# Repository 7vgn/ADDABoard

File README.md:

# AD/DA Board evolved
## An Add-On for the ATmega644(A) Evaluation Board

This is an add-on for the [EvaBoard evolved](https://github.com/7vgn/EvaBoard/) ATmega644(A) evaluation board. It is inspired by (and compatible with) the add-on board used in the lab course "Praktikum Systemprogrammierung" in the computer science curriculum at RWTH Aachen. It can be used both with the original [evaluation board](https://www.embedded.rwth-aachen.de/doku.php?id=lehre:atmegaevaboard) and its remake. 

This repository contains:

- A richly illustrated [Guide Book](Guide/ADDABoardGuide.pdf) with everything you need to know to build and use the board
- A [KiCAD project](KiCAD/) with the [Schematic](KiCAD/Schematic.pdf) and a PCB layout, ready to be manufactured
- The [bill of materials](BOM/BOM.pdf)
- [Test code](Tests/) for testing and debugging the board

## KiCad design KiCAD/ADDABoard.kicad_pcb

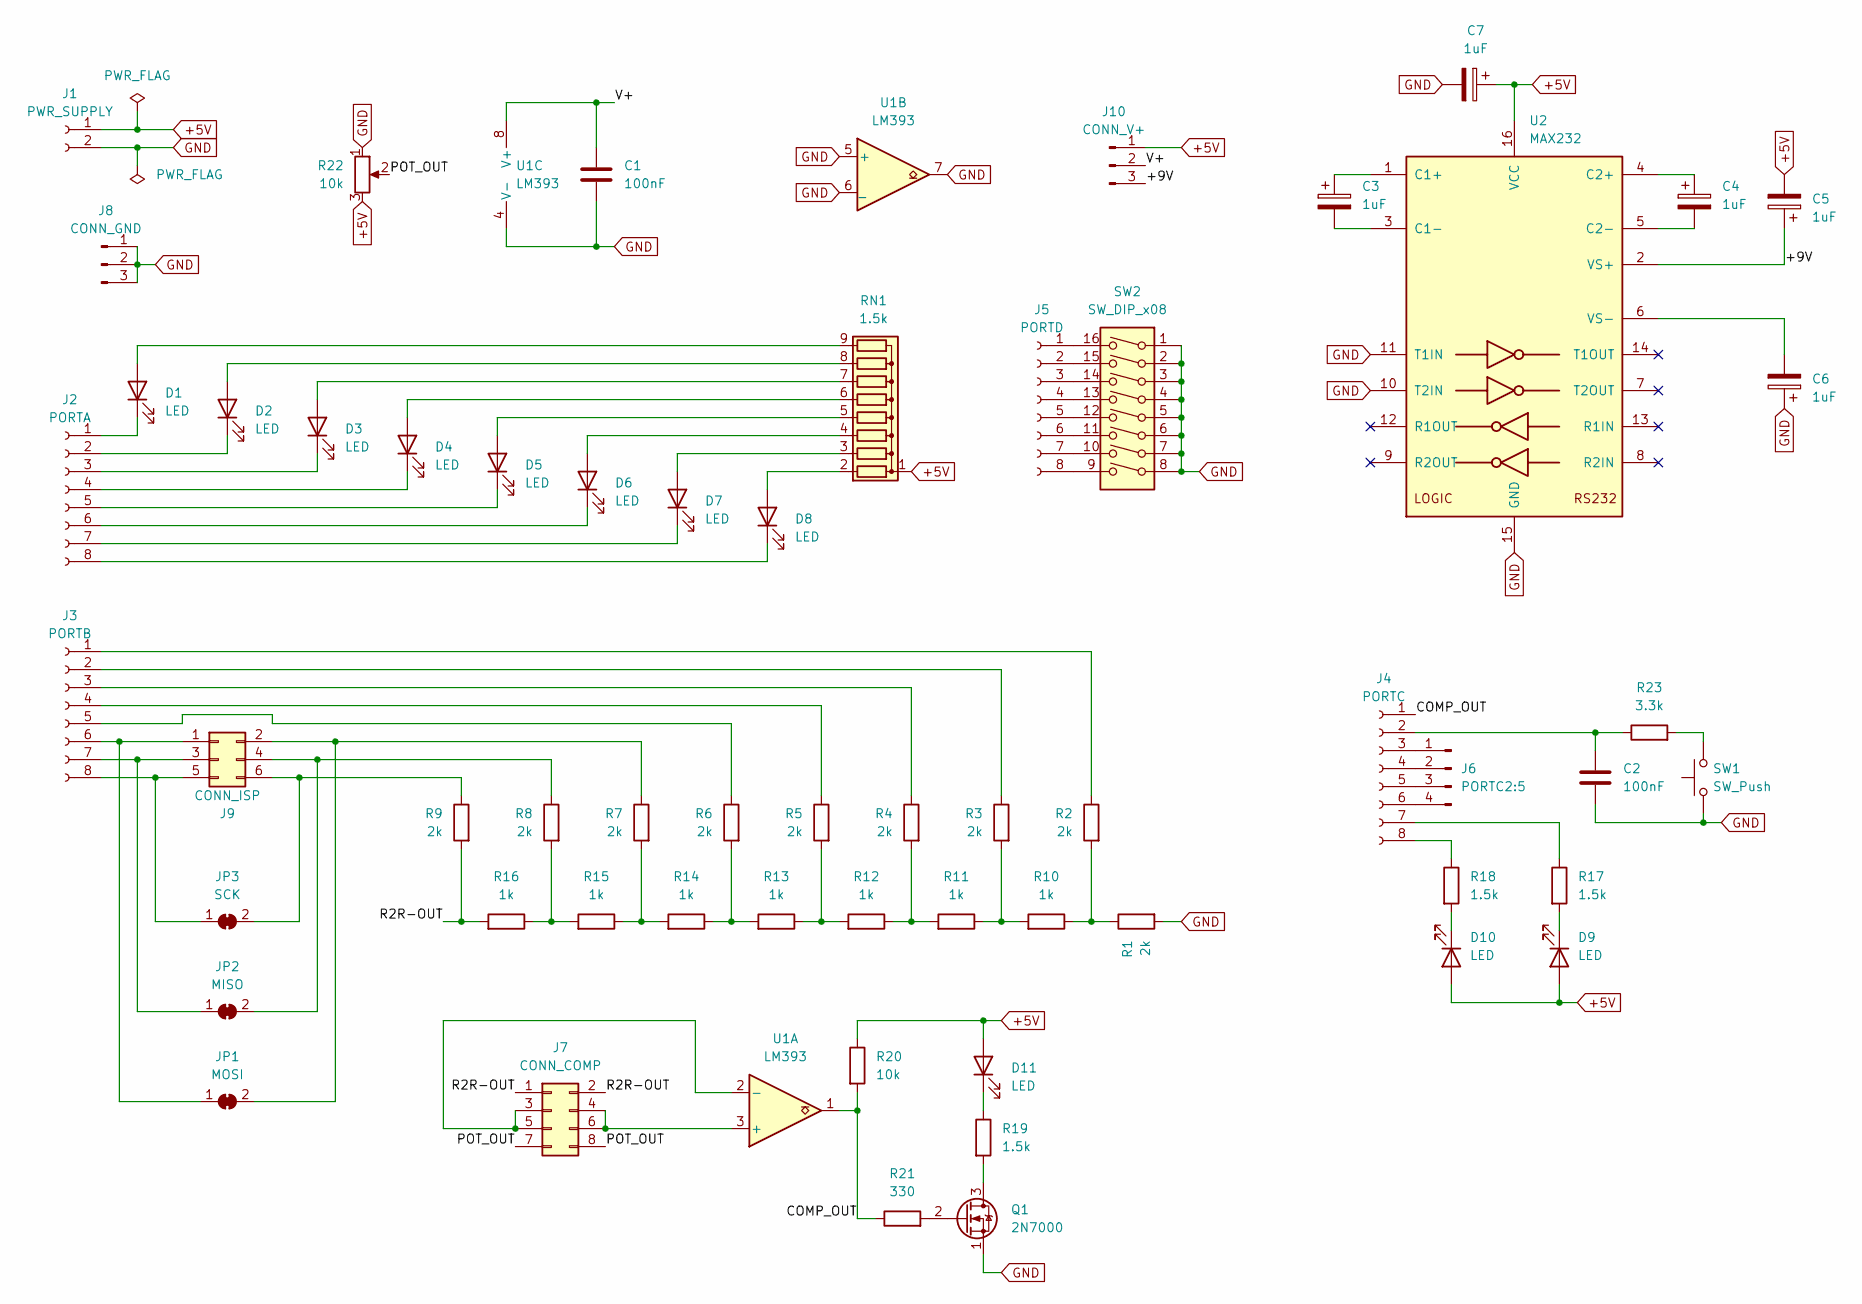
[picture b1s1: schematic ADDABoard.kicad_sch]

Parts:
C1, C2: 100nF; C_Disc_D5.0mm_W2.5mm_P5.00mm
C3, C4, C5, C6, C7: 1uF; CP_Radial_D5.0mm_P2.00mm
D1, D2, D3, D4, D5, D6, D7, D8, D9, D10, D11: LED; LED_D3.0mm
J1: PWR_SUPPLY; PinSocket_1x02_P2.54mm_Vertical
J2: PORTA; PinSocket_1x08_P2.54mm_Vertical
J3: PORTB; PinSocket_1x08_P2.54mm_Vertical
J4: PORTC; PinSocket_1x08_P2.54mm_Vertical
J5: PORTD; PinSocket_1x08_P2.54mm_Vertical
J6: PORTC2:5; PinHeader_1x04_P2.54mm_Vertical
J7: CONN_COMP; PinHeader_2x04_P2.54mm_Vertical
J8: CONN_GND; PinHeader_1x03_P2.54mm_Vertical
J9: CONN_ISP; PinHeader_2x03_P2.54mm_Vertical
J10: CONN_V+; PinHeader_1x03_P2.54mm_Vertical
JP1: MOSI; SolderJumper-2_P1.3mm_Bridged_RoundedPad1.0x1.5mm
JP2: MISO; SolderJumper-2_P1.3mm_Bridged_RoundedPad1.0x1.5mm
JP3: SCK; SolderJumper-2_P1.3mm_Bridged_RoundedPad1.0x1.5mm
Q1: 2N7000; TO-92_Inline
R1, R2, R3, R4, R5, R6, R7, R8, R9: 2k; R_Axial_DIN0207_L6.3mm_D2.5mm_P10.16mm_Horizontal
R10, R11, R12, R13, R14, R15, R16: 1k; R_Axial_DIN0207_L6.3mm_D2.5mm_P10.16mm_Horizontal
R17, R18, R19: 1.5k; R_Axial_DIN0207_L6.3mm_D2.5mm_P10.16mm_Horizontal
R20: 10k; R_Axial_DIN0207_L6.3mm_D2.5mm_P10.16mm_Horizontal
R21: 330; R_Axial_DIN0207_L6.3mm_D2.5mm_P10.16mm_Horizontal
R22: 10k; Potentiometer_Alps_RK09K_Single_Horizontal
R23: 3.3k; R_Axial_DIN0207_L6.3mm_D2.5mm_P10.16mm_Horizontal
RN1: 1.5k; R_Array_SIP9
SW1: SW_Push; SW_PUSH_6mm
SW2: SW_DIP_x08; SW_DIP_SPSTx08_Slide_9.78x22.5mm_W7.62mm_P2.54mm
U1: LM393; DIP-8_W7.62mm
U2: MAX232; DIP-16_W7.62mm

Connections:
+5V: C5.2, C7.1, D9.2 (A), D10.2 (A), D11.2 (A), J1.1, J10.1, R20.1, R22.3, RN1.1 (common), U2.16 (VCC)
/+9V: C5.1, J10.3, U2.2 (VS+)
/COMP_OUT: J4.1, R20.2, R21.1, U1.1
/POT_OUT: J7.7, J7.8, R22.2
/R2R-OUT: J7.1, J7.2, R9.2, R16.2
/V+: C1.1, J10.2, U1.8 (V+)
GND: C1.2, C2.2, C6.1, C7.2, J1.2, J8.1, J8.2, J8.3, Q1.1 (S), R1.2, R22.1, SW1.1, SW2.1, SW2.2, SW2.3, SW2.4, SW2.5, SW2.6, SW2.7, SW2.8, U1.4 (V-), U1.5 (+), U1.6 (_), U1.7, U2.10 (T2IN), U2.11 (T1IN), U2.15 (GND)
unnamed: C2.1, J4.2, R23.1
unnamed: C3.1, U2.1 (C1+)
unnamed: C3.2, U2.3 (C1-)
unnamed: C4.1, U2.4 (C2+)
unnamed: C4.2, U2.5 (C2-)
unnamed: C6.2, U2.6 (VS-)
unnamed: D1.1 (K), J2.1
unnamed: D1.2 (A), RN1.9 (R8)
unnamed: D2.1 (K), J2.2
unnamed: D2.2 (A), RN1.8 (R7)
unnamed: D3.1 (K), J2.3
unnamed: D3.2 (A), RN1.7 (R6)
unnamed: D4.1 (K), J2.4
unnamed: D4.2 (A), RN1.6 (R5)
unnamed: D5.1 (K), J2.5
unnamed: D5.2 (A), RN1.5 (R4)
unnamed: D6.1 (K), J2.6
unnamed: D6.2 (A), RN1.4 (R3)
unnamed: D7.1 (K), J2.7
unnamed: D7.2 (A), RN1.3 (R2)
unnamed: D8.1 (K), J2.8
unnamed: D8.2 (A), RN1.2 (R1)
unnamed: D9.1 (K), R17.2
unnamed: D10.1 (K), R18.2
unnamed: D11.1 (K), R19.1
unnamed: J3.1, R2.1
unnamed: J3.2, R3.1
unnamed: J3.3, R4.1
unnamed: J3.4, R5.1
unnamed: J3.5, R6.1
unnamed: J3.6, J9.1, JP1.1 (A)
unnamed: J3.7, J9.3, JP2.1 (A)
unnamed: J3.8, J9.5, JP3.1 (A)
unnamed: J4.3, J6.1
unnamed: J4.4, J6.2
unnamed: J4.5, J6.3
unnamed: J4.6, J6.4
unnamed: J4.7, R17.1
unnamed: J4.8, R18.1
unnamed: J5.1, SW2.16
unnamed: J5.2, SW2.15
unnamed: J5.3, SW2.14
unnamed: J5.4, SW2.13
unnamed: J5.5, SW2.12
unnamed: J5.6, SW2.11
unnamed: J5.7, SW2.10
unnamed: J5.8, SW2.9
unnamed: J7.3, J7.5, U1.2 (-)
unnamed: J7.4, J7.6, U1.3 (+)
unnamed: J9.2, JP1.2 (B), R7.1
unnamed: J9.4, JP2.2 (B), R8.1
unnamed: J9.6, JP3.2 (B), R9.1
unnamed: Q1.2 (G), R21.2
unnamed: Q1.3 (D), R19.2
unnamed: R1.1, R2.2, R10.1
unnamed: R3.2, R10.2, R11.1
unnamed: R4.2, R11.2, R12.1
unnamed: R5.2, R12.2, R13.1
unnamed: R6.2, R13.2, R14.1
unnamed: R7.2, R14.2, R15.1
unnamed: R8.2, R15.2, R16.1
unnamed: R23.2, SW1.2

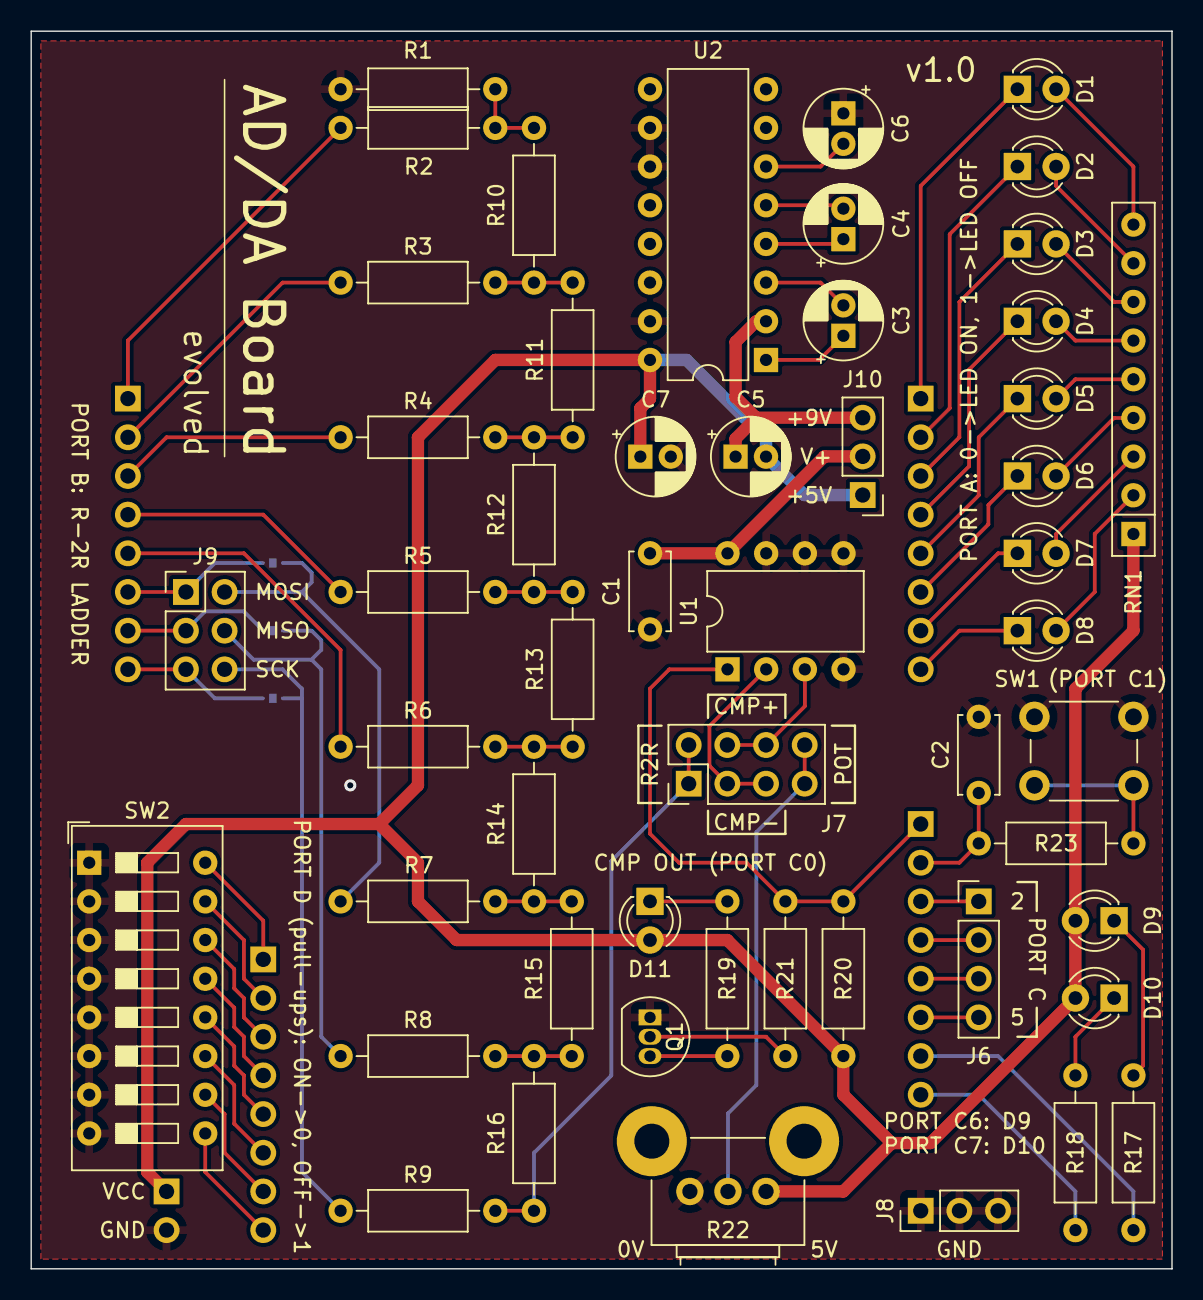
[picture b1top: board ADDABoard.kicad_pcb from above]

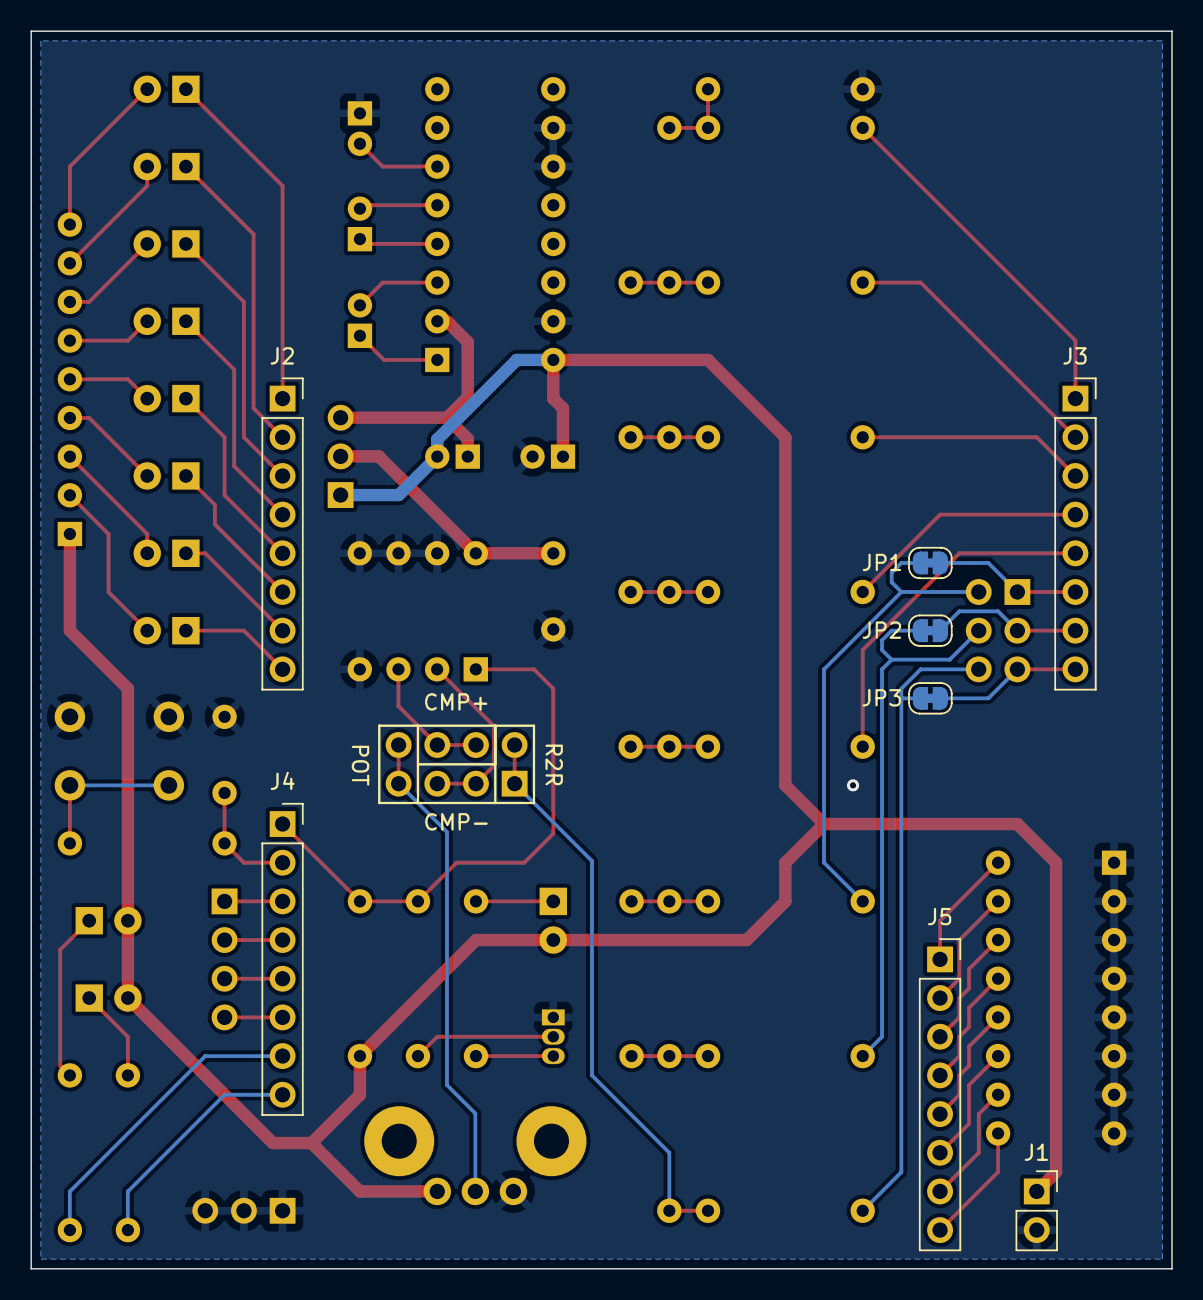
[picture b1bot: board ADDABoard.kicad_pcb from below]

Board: 2 copper layers, 74.9 x 81.3 mm, 60 parts (8 on the bottom side), 69 nets.

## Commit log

2025-09-14 Added missing resistor to BOM
